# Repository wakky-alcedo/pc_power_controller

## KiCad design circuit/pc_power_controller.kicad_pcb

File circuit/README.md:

# pc_power_controller — KiCad プロジェクト

ESP32 で PC電源ボタン（PWR_SW）をフォトMOSリレー経由でON/OFFし、PLED（電源LED）の
点灯状態をフォトカプラ経由で監視するための回路の「回路図」と、ユニバーサル基板への
手配線を前提とした「部品配置＋ラッツネスト確認用PCBレイアウト」です。
**銅箔パターンは作成していません**（配線ガイド用途のみ）。

## ファイル構成

```
circuit/
├── pc_power_controller.kicad_sch   回路図
├── pc_power_controller.kicad_pcb   PCBレイアウト（配置のみ、ルーティング無し）
├── pc_power_controller.kicad_pro   プロジェクトファイル
├── sym-lib-table                  プロジェクト用シンボルライブラリテーブル
├── fp-lib-table                   プロジェクト用フットプリントライブラリテーブル
├── Local.kicad_sym                 自作シンボル（4pinオプトカプラ代替 / XIAO ESP32C3）
├── Local.pretty/
│   └── Seeed_XIAO_ESP32C3.kicad_mod  自作フットプリント（XIAO ESP32C3用）
├── pc_power_controller.net         回路図から書き出したネットリスト（参考用）
├── erc_report.txt / erc_report.json  ERC結果
├── pcb_drc.txt                     PCB DRC結果（未配線=ラッツネスト11本を含む）
├── BOM.md                          部品表（秋月電子リンク付き）
├── scripts/
│   ├── gen_sch.py                  回路図生成スクリプト
│   ├── gen_pcb.py                  PCB自動生成スクリプト（KiCad付属pythonで実行）
│   └── gen_ratsnest_svg.py         配置＋ラッツネストのSVG可視化を書き出すスクリプト
└── output/
    └── placement_guide.svg         配置＋ラッツネストの可視化（SVG）
```

## 開き方

1. KiCad 10.0 系で `pc_power_controller.kicad_pro` を開く（プロジェクトマネージャ経由）。
2. 「回路図エディタ」で `pc_power_controller.kicad_sch` を確認できます。
3. 「PCBエディタ」で `pc_power_controller.kicad_pcb` を開くと、部品が配置された状態で、
   配線されていないネットが**ラッツネスト（黄色い破線のエアワイヤー）として自動的に
   表示されます**（KiCadのPCBエディタは接続情報から自動でラッツネストを描画するため、
   ファイルには線そのものは保存されていません）。
   - ラッツネストが表示されない場合は、メニュー「編集」→「ボードの再構築」
     または表示メニューでラッツネスト表示をONにしてください（デフォルトでON）。

## ERC / DRC 結果

- 回路図ERC: **エラー0件**（`erc_report.txt`）。警告は、手作業で構築したため
  ライブラリキャッシュと実ライブラリのシンボル定義が完全一致しない旨の
  `lib_symbol_mismatch` と、汎用シンボルのピン間隔(1.27mm)由来の
  `endpoint_off_grid` のみで、接続には影響しません。
- PCB DRC: **違反0件、未配線アイテム11件**（`pcb_drc.txt`）。この11件が
  そのまま「ラッツネスト」として表示される未配線のネット接続です
  （= 意図的に配線していない状態）。

## 回路構成の要点

- **XIAO ESP32C3 (U3) D1/GPIO3** → R1(330Ω) → TLP225A(F)(U1) → J1 (PWR_SW_HEADER, 2P)
- J2 (PLED_HEADER, 2P) → TLP621-1(U2) → **XIAO ESP32C3 (U3) D2/GPIO4**
  （R2=10kΩでプルアップ）
- GND / 3V3 はすべて U3（XIAO ESP32C3）のGND / 3V3ピンに集約
  （3V3はXIAO本体のレギュレータ出力をそのまま基板側の電源として使う想定）
- D1/D2（GPIO3/GPIO4）を選んでいるのは、GPIO2・GPIO8・GPIO9
  （XIAOのD0・D8・D9）が ESP32-C3 のストラッピングピンで起動時の挙動に
  影響するため、それらを避けたためです。
- U1は当初TLP222AFを想定していましたが**秋月電子で在庫切れのため
  TLP225A(F)に変更**しています（同一パッケージ・同一ピン配置のため
  回路・フットプリントは変更なし）。
- ESP32本体・TLP225A(F)・TLP621-1 は標準ライブラリに厳密一致するシンボルが無いため、
  以下のように代用しています（各シンボルの `Note` プロパティにも明記済み）。
  - **Seeed XIAO ESP32C3**: 自作シンボル (`Local:Seeed_XIAO_ESP32C3`) ＋
    自作フットプリント (`Local:Seeed_XIAO_ESP32C3`、`Local.pretty/` に格納)。
    XIAO本体は基板に直接ハンダ付けせず、2×7・2.54mmピッチの丸ピンICソケット
    経由で着脱する前提のフットプリントです（詳細はBOM.md）。

### XIAOのピン配置（重要）

Seeed公式のピン配置資料で実機を確認したところ、5V/GND/3V3はUSBコネクタ側の
先頭ピンではなく、**右列の末尾に固まって配置**されています。本プロジェクトの
シンボル・フットプリントは以下の実物理配置に合わせてあります。

| 物理ピン番号 | 左列 (USB側が上) | | 物理ピン番号 | 右列 (USB側が上) |
|---|---|---|---|---|
| 1 | D0 / GPIO2 (ストラッピング) | | 8 | D7 / GPIO20 |
| 2 | **D1 / GPIO3 → リレー制御** | | 9 | D8 / GPIO8 (ストラッピング) |
| 3 | **D2 / GPIO4 → PLED監視** | | 10 | D9 / GPIO9 (ストラッピング) |
| 4 | D3 / GPIO5 | | 11 | D10 / GPIO10 |
| 5 | D4 / GPIO6 (SDA) | | 12 | **3V3** |
| 6 | D5 / GPIO7 (SCL) | | 13 | **GND** |
| 7 | D6 / GPIO21 (TX) | | 14 | 5V (未使用) |

（列内は上から下がピン1→7、右列は下から上がピン8→14。KiCadの
`Local:Seeed_XIAO_ESP32C3` シンボルおよび `Local.pretty/Seeed_XIAO_ESP32C3.kicad_mod`
フットプリントのピン番号は上表と完全に一致しています。）
  - TLP225A(F) / TLP621-1: 自作の汎用4pinオプトカプラシンボル
    (`Local:Optocoupler_Generic_4Pin`、`Local.kicad_sym` に格納) ＋
    フットプリント `Package_DIP:DIP-4_W7.62mm_Socket`（ICソケット実装想定）

## 基板サイズを変更したい場合

想定している基板サイズは **秋月電子 片面ガラス・ユニバーサル基板 Bタイプ (95×72mm)**
です（`BOM.md` 参照）。手持ちの基板サイズが異なる場合は、

1. `circuit/scripts/gen_pcb.py` を開き、冒頭付近の
   ```python
   BOARD_W = 95.0
   BOARD_H = 72.0
   ```
   を実際のサイズ(mm)に書き換える。
2. KiCad付属のPythonでスクリプトを再実行して `.kicad_pcb` を再生成する。
   ```
   "C:\Program Files\KiCad\10.0\bin\python.exe" circuit\scripts\gen_pcb.py
   ```
   （PCBエディタでEdge.Cutsの矩形を直接ドラッグして編集しても構いません）
3. 部品配置がボード外に出ていないか、PCBエディタで確認してください。

## 配置＋ラッツネストの画像（PNG）について

kicad-cli にはラッツネスト（未配線エアワイヤー）を含めてSVG/PNGへ書き出す機能が
無く、ラッツネストはPCBエディタ上でのみ動的に計算・表示される情報のため、
`kicad-cli pcb export svg` 等では再現できません。

代わりに、`circuit/scripts/gen_ratsnest_svg.py` で `.kicad_pcb` の接続情報
（`BuildConnectivity()`）から各ネットの未配線ペアを取得し、独自にラッツネスト線を
描画したSVGを `circuit/output/placement_guide.svg` として生成しています
（黄色の破線 = ラッツネスト）。そのままブラウザ等で開いて確認できます。
PNG化したい場合は、このSVGをブラウザで開いてスクリーンショットを撮るか、
Inkscape等で `placement_guide.svg` → PNG に変換してください。

実際のPCBエディタでの見た目を確認したい場合は、上記「開き方」の手順で
PCBエディタを開いてください（GUI上のラッツネスト表示が最も正確です）。

再生成する場合:
```
"C:\Program Files\KiCad\10.0\bin\python.exe" circuit\scripts\gen_ratsnest_svg.py
```

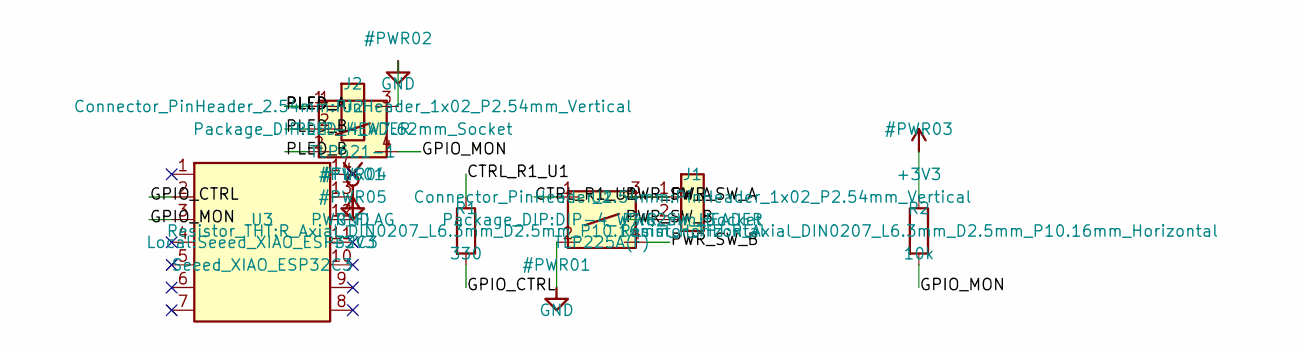
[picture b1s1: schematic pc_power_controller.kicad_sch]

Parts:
J1: PWR_SW_HEADER; PinHeader_1x02_P2.54mm_Vertical
J2: PLED_HEADER; PinHeader_1x02_P2.54mm_Vertical
R1: 330; R_Axial_DIN0207_L6.3mm_D2.5mm_P10.16mm_Horizontal
R2: 10k; R_Axial_DIN0207_L6.3mm_D2.5mm_P10.16mm_Horizontal
U1: TLP225A(F); DIP-4_W7.62mm_Socket
U2: TLP621-1; DIP-4_W7.62mm_Socket
U3: Seeed_XIAO_ESP32C3

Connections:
3V3: R2.1, U3.12 (3V3)
GND: U1.2, U2.3, U3.13 (GND)
GPIO_CTRL: R1.2, U3.2 (D1/GPIO3)
GPIO_MON: R2.2, U2.4, U3.3 (D2/GPIO4)
PLED_A: J2.1, U2.1
PLED_B: J2.2, U2.2
PWR_SW_A: J1.1, U1.3
PWR_SW_B: J1.2, U1.4
R1_U1: R1.1, U1.1

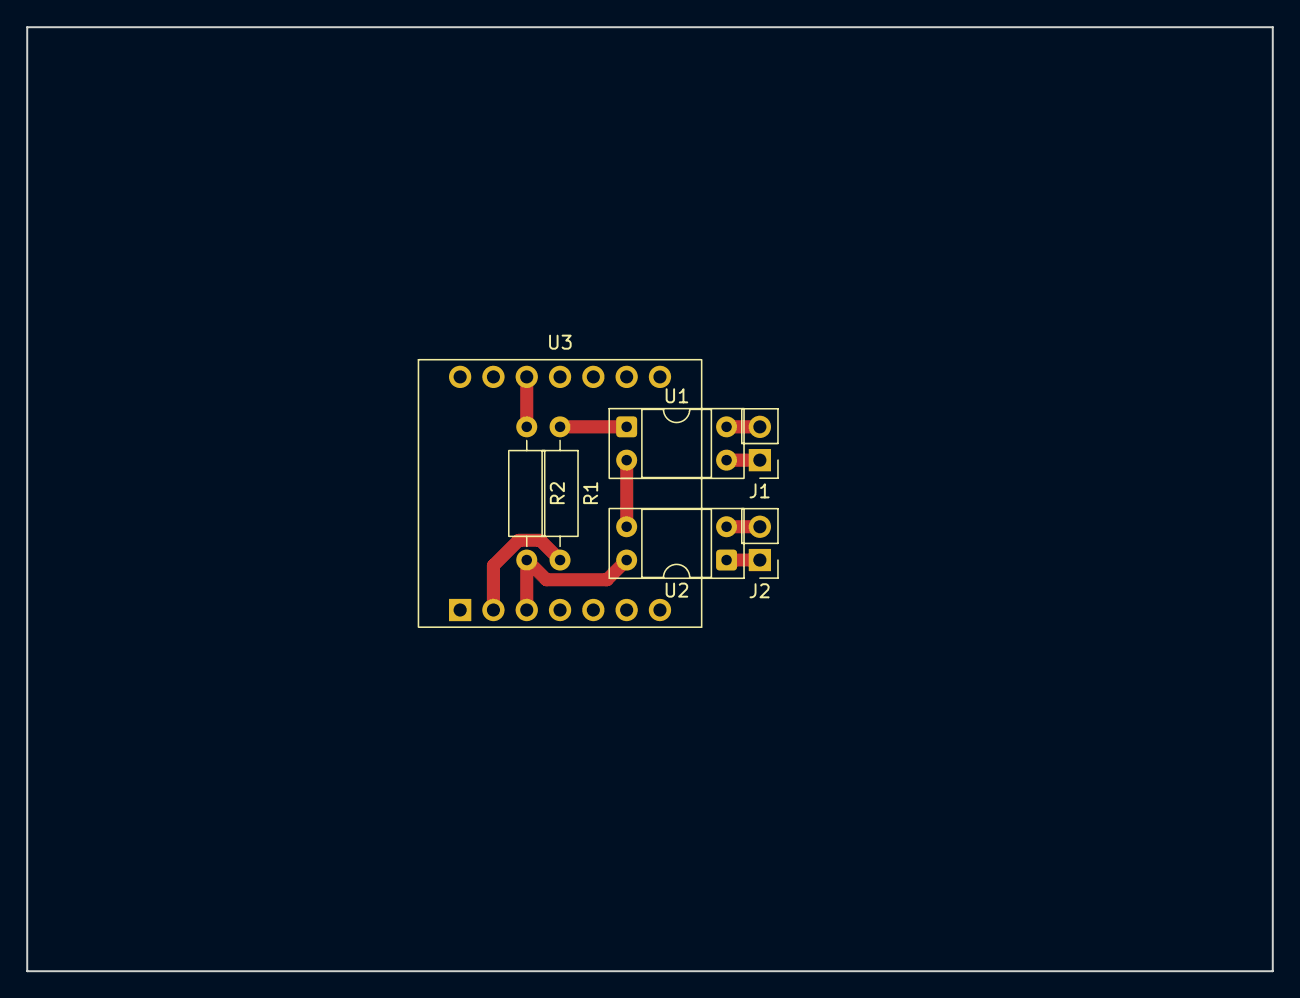
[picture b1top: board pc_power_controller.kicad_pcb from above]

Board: 2 copper layers, 95.0 x 72.0 mm, 7 parts (0 on the bottom side), 9 nets.

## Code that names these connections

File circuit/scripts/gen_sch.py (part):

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          (number "1" (effects (font (size 1.27 1.27))))
        )
        (pin bidirectional line (at -10.16 5.08 0) (length 2.54)
          (name "D1/GPIO3" (effects (font (size 1.27 1.27))))
          (number "2" (effects (font (size 1.27 1.27))))
        )
        (pin bidirectional line (at -10.16 2.54 0) (length 2.54)
          (name "D2/GPIO4" (effects (font (size 1.27 1.27))))
          (number "3" (effects (font (size 1.27 1.27))))
        )
        (pin bidirectional line (at -10.16 0 0) (length 2.54)
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# XIAO, power) has pin offsets that are themselves exact 2.54mm multiples, so
# their own origins land on-grid too.

# CONTROL PATH (XIAO D1/GPIO3 -> R1 -> U1(TLP225A(F)) -> J1 PWR_SW_HEADER)
R1_pos = (38.1, 34.29)
p_R1_1 = u(); p_R1_2 = u()
add_symbol("Device:R", "R1", "330", R1_pos, 0,
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p_GND1 = u()
add_symbol("power:GND", "#PWR01", "GND", GND1_pos, 0, {"1": p_GND1}, in_bom=False, on_board=False)

# MONITOR PATH (PLED_HEADER J2 -> U2(TLP621-1) -> GND / GPIO_MON, R2 pullup to 3V3)
J2_pos = (25.4, 20.32)
p_J2_1 = u(); p_J2_2 = u()
add_symbol("Connector_Generic:Conn_01x02", "J2", "PLED_HEADER", J2_pos, 0,
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           {"1": p_R2_1, "2": p_R2_2}, footprint="Resistor_THT:R_Axial_DIN0207_L6.3mm_D2.5mm_P10.16mm_Horizontal")

PWR3V3_1_pos = (88.9, 25.4)  # above R2 pin1 -- must NOT share y with the
                              # GPIO_MON stub on R2 pin2, or the straight
                              # vertical wire down to it would electrically
                              # merge the two nets
p_3V3_1 = u()
add_symbol("power:+3V3", "#PWR03", "+3V3", PWR3V3_1_pos, 0, {"1": p_3V3_1}, in_bom=False, on_board=False)

# Seeed XIAO ESP32C3 module (U3). D1/GPIO3 drives the control path, D2/GPIO4
# reads the monitor path. Both are ordinary GPIOs on the C3 (no ADC/strapping
# concerns); GPIO2/GPIO8/GPIO9 (D0/D8/D9) are avoided since those are strapping
# pins on ESP32-C3.
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xiao_pins = {str(i): u() for i in range(1, 15)}
add_symbol("Local:Seeed_XIAO_ESP32C3", "U3", "Seeed_XIAO_ESP32C3", XIAO_pos, 0,
           xiao_pins, footprint="Local:Seeed_XIAO_ESP32C3",
           extra_props=[("Note", "Seeed Studio XIAO ESP32C3, mounted on 2x7 2.54mm female headers. Pin2=D1/GPIO3 (relay control out), Pin3=D2/GPIO4 (PLED monitor in). Pin order matches Seeed's real silkscreen: left column D0-D6 (pins 1-7), right column D7-D10,3V3,GND,5V (pins 8-14)")])

GND3_pos = (25.4, 30.48)  # coincides with XIAO pin13 (GND)
p_GND3 = u()
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    wire(pin, end)
    label(text, end)

# ---- Control path: XIAO D1/GPIO3 -> R1 -> U1(TLP225A(F)) -> J1 (PWR_SW_HEADER) ----
stub_label(XIAO_pin[2], (-1, 0), "GPIO_CTRL")
stub_label(R1_p2, (0, 1), "GPIO_CTRL")

stub_label(R1_p1, (0, -1), "CTRL_R1_U1")
stub_label(U1_p1, (-1, 0), "CTRL_R1_U1")

route(U1_p2, GND1_pos)

stub_label(U1_p3, (1, 0), "PWR_SW_A")
stub_label(J1_p1, (-1, 0), "PWR_SW_A")
stub_label(U1_p4, (1, 0), "PWR_SW_B")
stub_label(J1_p2, (-1, 0), "PWR_SW_B")

# ---- Monitor path: J2 (PLED_HEADER) -> U2(TLP621-1) -> GND / XIAO D2/GPIO4 (+ R2 pull-up) ----
stub_label(J2_p1, (-1, 0), "PLED_A")
stub_label(U2_p1, (-1, 0), "PLED_A")
stub_label(J2_p2, (-1, 0), "PLED_B")
stub_label(U2_p2, (-1, 0), "PLED_B")

route(U2_p3, GND2_pos)

stub_label(U2_p4, (1, 0), "GPIO_MON")
stub_label(R2_p2, (0, 1), "GPIO_MON")
stub_label(XIAO_pin[3], (-1, 0), "GPIO_MON")

route(R2_p1, PWR3V3_1_pos)

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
